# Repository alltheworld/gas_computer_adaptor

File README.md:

# gas_computer_adaptor
gas_computer_adaptor schematics

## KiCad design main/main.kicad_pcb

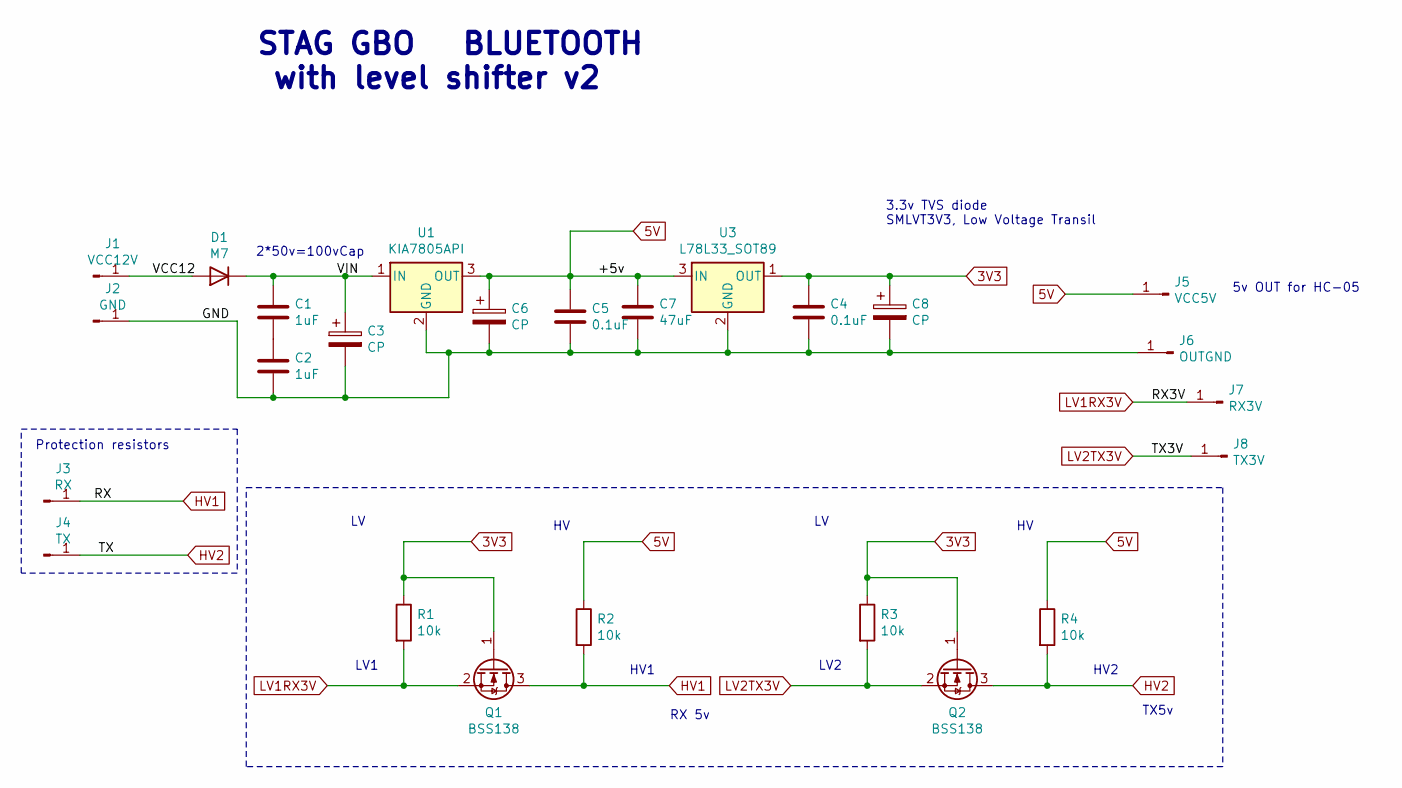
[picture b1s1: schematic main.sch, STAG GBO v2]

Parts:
C1, C2: 1uF; C_0603_1608Metric_Pad1.05x0.95mm_HandSolder
C3, C6: CP; CP_Elec_6.3x3
C4, C5: 0.1uF; C_0603_1608Metric_Pad1.05x0.95mm_HandSolder
C7: 47uF; C_0805_2012Metric_Pad1.15x1.40mm_HandSolder
C8: CP; CP_EIA-7343-30_AVX-N_Pad2.25x2.55mm_HandSolder
D1: M7; D_SMA
J1: VCC12V; PinHeader_1x01_P2.54mm_Vertical
J2: GND; PinHeader_1x01_P2.54mm_Vertical
J3: RX; PinHeader_1x01_P2.54mm_Vertical
J4: TX; PinHeader_1x01_P2.54mm_Vertical
J5: VCC5V; PinHeader_1x01_P2.54mm_Vertical
J6: OUTGND; PinHeader_1x01_P2.54mm_Vertical
J7: RX3V; PinHeader_1x01_P2.54mm_Vertical
J8: TX3V; PinHeader_1x01_P2.54mm_Vertical
Q1, Q2: BSS138; SOT-23
R1, R2, R3, R4: 10k; R_0805_2012Metric_Pad1.15x1.40mm_HandSolder
U1: KIA7805API; TO-220-3_Horizontal_TabDown
U3: L78L33_SOT89; SOT-89-3

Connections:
3V3: C4.1, C8.1, Q1.1 (G), Q2.1 (G), R1.1, R3.1, U3.1 (OUT)
5V: C5.1, C6.1, C7.1, J5.1, R2.1, R4.1, U1.3 (OUT), U3.3 (IN)
/GND: C2.2, C3.2, C4.2, C5.2, C6.2, C7.2, C8.2, J2.1, J6.1, U1.2 (GND), U3.2 (GND)
/VCC12: D1.2 (A), J1.1
/VIN: C1.1, C3.1, D1.1 (K), U1.1 (IN)
HV1: J3.1, Q1.3 (D), R2.2
HV2: J4.1, Q2.3 (D), R4.2
LV1RX3V: J7.1, Q1.2 (S), R1.2
LV2TX3V: J8.1, Q2.2 (S), R3.2
unnamed: C1.2, C2.1

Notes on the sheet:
LV1
HV1
LV2
HV2
2*50v=100vCap
Protection resistors
RX 5v
TX5v
STAG GBO BLUETOOTH with level shifter v2
3.3v TVS diode SMLVT3V3, Low Voltage Transil
5v OUT for HC-05

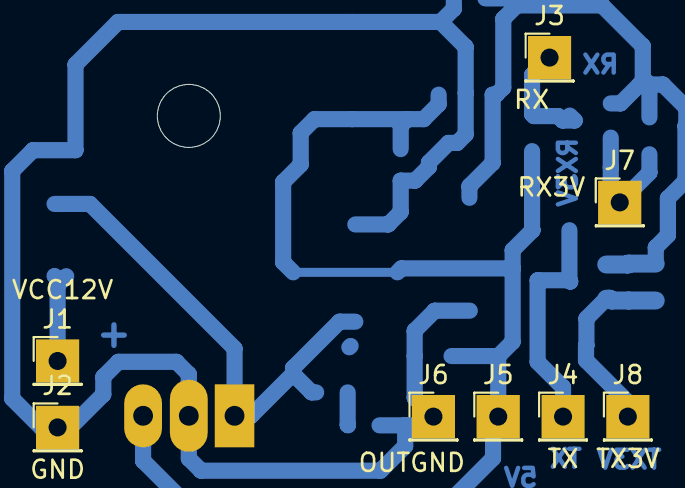
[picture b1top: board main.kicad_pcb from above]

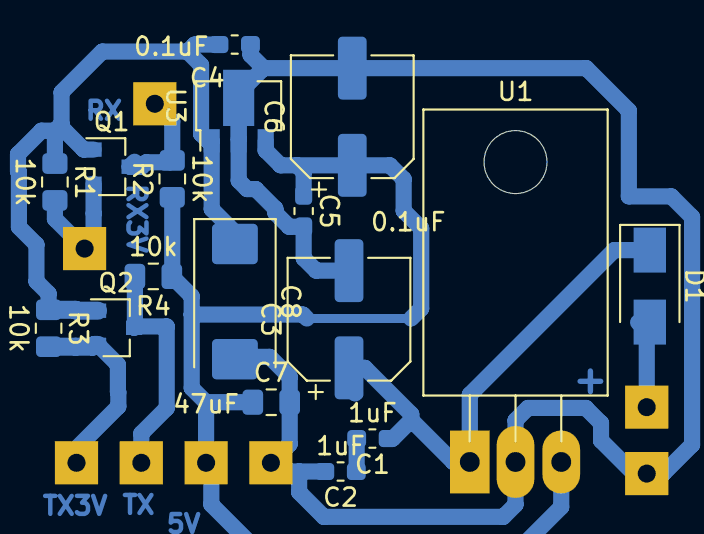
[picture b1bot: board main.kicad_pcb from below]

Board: 2 copper layers, 25 parts (17 on the bottom side), 10 nets.

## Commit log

2020-01-31 init
